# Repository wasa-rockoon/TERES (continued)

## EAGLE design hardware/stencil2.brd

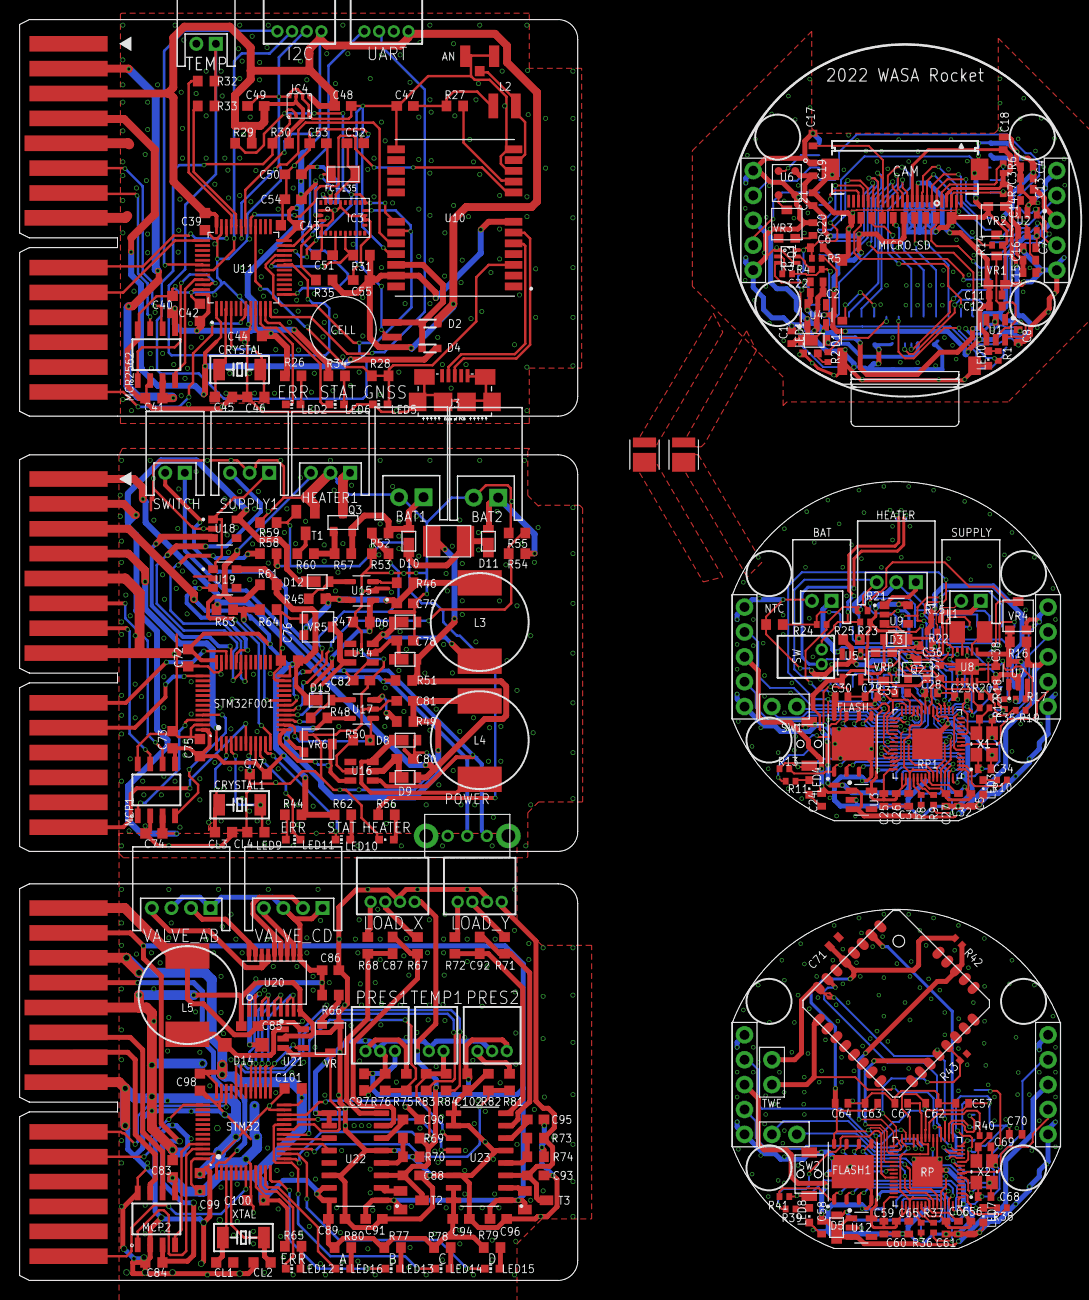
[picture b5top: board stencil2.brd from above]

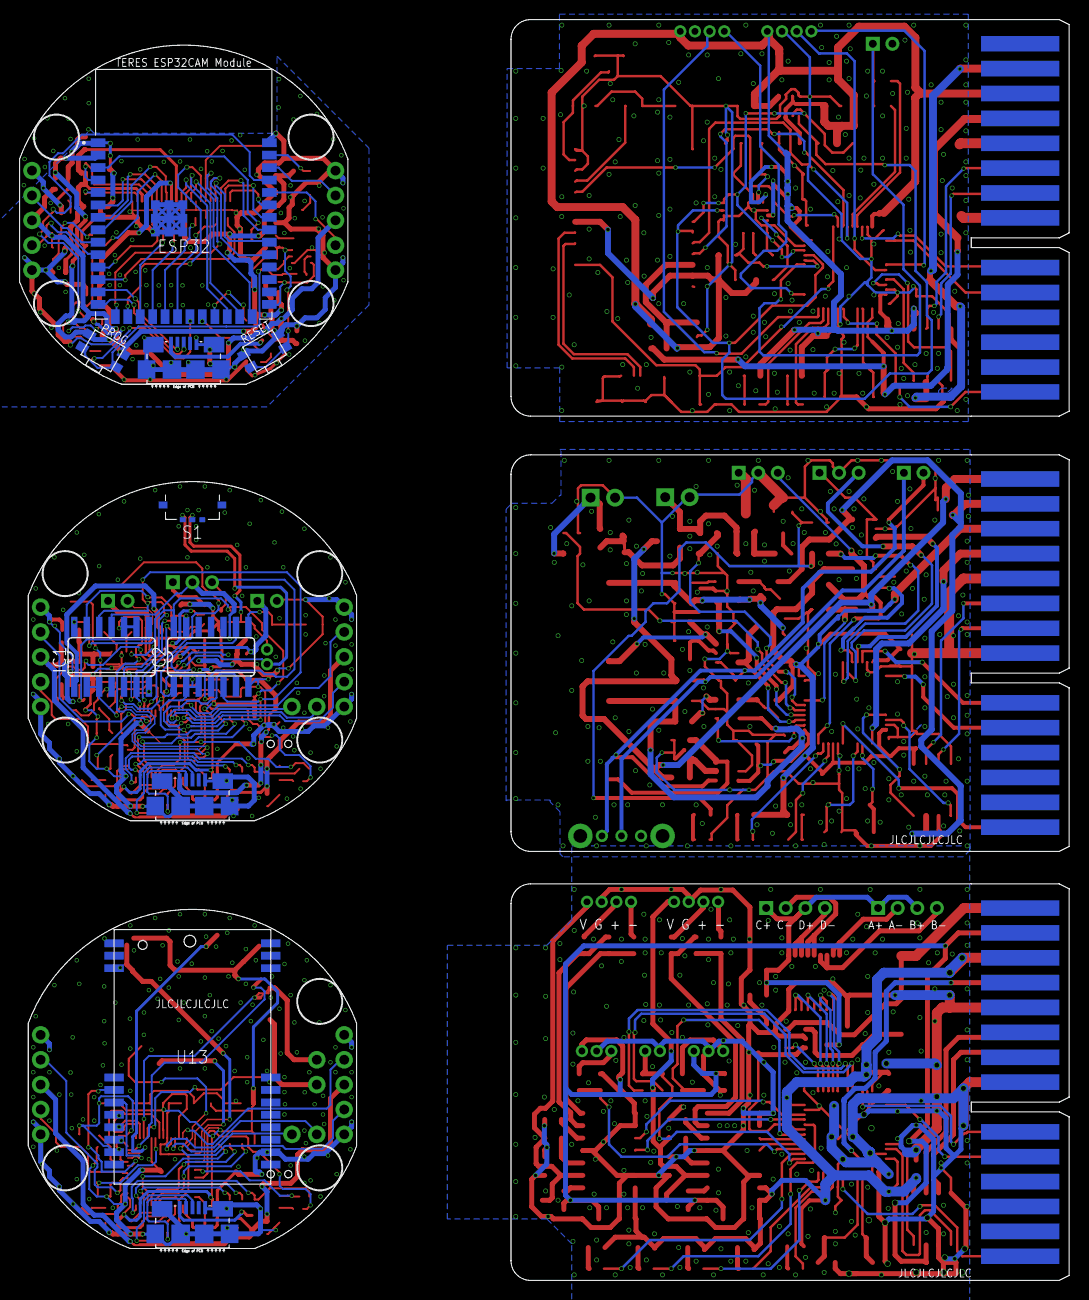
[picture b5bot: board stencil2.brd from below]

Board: 2 copper layers, 107.2 x 128.8 mm, 331 parts (10 on the bottom side), 303 nets.

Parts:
AB: S4B-PH-K-S
AN: U.FL-R-SMT; U.FL_SMT
BAT: S2B-PH-K-S
BAT1, BAT2: S2B-XH-A
BOTTOM, BOTTOM1: P5_2.54
C1, C4, C6, C7, C13, C18, C19, C24, C37, C58: 0.1µF; C0402
C2, C21, C25, C30, C36, C38, C59: 10µF; C0402
C3: 22µF; C0402
C5, C23, C27, C28, C29, C32, C33, C56, C57, C61, C62, C63, C70, C71: 0.1µ; C0402
C8, C14: 0.01µF; C0402
C9, C10: P5_2.54
C11, C20: 2.2µF; C0402
C12, C16: 100pF; C0402
C15: 1.0µF; C0402
C17: 15pF; C0402
C22: 1µF; C0402
C26, C31, C60, C65: 1µ; C0402
C34, C35: 10p; C0402
C39, C40, C41, C42, C43, C44, C72, C73, C74, C75, C76, C77, C83, C84, C98, C99, C100, C101: C0603K
C45, C46: 15pF; C0603K
C47: 47pF; C0603
C48, C49, C50, C51, C55: 0.1µ; C0603
C52, C53, C97, C102: C0603
C54, C82, C87, C89, C90, C92, C94, C95: 0.1µF; C0603
C64, C68, C69: 0.1μ; C0402
C66, C67: 1μ; C0402
C78, C79, C80, C81: 47µF; C0603
C85: 4.7µF; C0603
C86: 2.2µF; C0603
C88, C91, C93, C96: 10µF; C0603
CAM: OV2640_FPC_INV; FH12-24S-0.5SH
CD: S4B-PH-K-S
CELL: DCK-3R3E; DC,DCK
CL1, CL2, CL3, CL4: 15pF; C0603K
CRYSTAL, CRYSTAL1: 32.768kHz; FC-255
D1, D3, D5, D6, D7, D8, D9, D10, D11, D12, D13: CUHS20S30
D2, D4: RB521S-30TE61; SODFL1608X70N
D14: SOD123
ESP32: ESP32-S3-WROOM-1-N16R2; XCVR_ESP32-S3-WROOM-1-N16R2
FC-135: FC-135
FLASH, FLASH1: W25Q32JVZPIQ; SON127P600X500X80-9N
HEATER, HEATER1: S3B-PH-K-S
I2C: S4B-ZR
IC1, IC2: 4066D; SO14
IC3: BN055; LGA-28_3.80X5.20/0.5
IC4: BME280
J1, J2, J3, J4: MICRO_USB_B_HIROSE_ZX62-B-5PA(11)MODEL; GHI-CONNECTORS_10118192-0001LF(MICRO-USB-B-AMPHENOL-FCI)
L1: 4.7µH; L3225M
L2: 33Ω; SM-NE29
L3, L4: 22µH; NR10050
L5: 10µH; NR10050
LED0, LED1, LED3, LED4, LED7, LED8, LED10: CHIPLED_0603
LED2, LED5, LED6, LED9, LED11, LED12, LED13, LED14, LED15, LED16: CHIP-LED0603
LOAD_X: S4B-ZR
LOAD_Y: S4B-ZR
MCP1, MCP2, MCP2562: MCP2562-E/SN; SOIC127P600X175-8N
MICRO_SD: DM3AT-SF-PEJM5; HRS_DM3AT-SF-PEJM5
NTC: 10k; R0603
POWER: SK-12D01-VG4
PRES1, PRES2: S3B-ZR
PROG: THAF01-NC-R
Q1: HN1C01FU; SOT-363
Q2, Q3: IRLML6402; SOT-23
R1, R2, R12, R13, R14, R38, R39, R40, R41: 1k; R0402
R3, R4, R5, R6, R7, R18, R21, R24, R42, R43: 10k; R0402
R8, R9: 27.4; R0402
R10, R17, R23: 100; R0402
R11: 220; R0402
R15, R19, R20, R22: 100k; R0402
R16, R25, R45, R48: 0.033; R0603
R26, R28, R29, R30, R31, R34, R35: R0603
R27: 10; R0603
R32, R47, R50, R51, R57, R59, R61, R70, R74, R75, R81, R83: 10k; R0603
R33, R53, R55, R64, R84: 100k; R0603
R36, R37: 27Ω; R0402
R44, R58, R60, R62, R65, R77, R78, R79, R80: 1k; R0603
R46, R49, R67, R68, R71, R72: 100; R0603
R52, R54, R63, R66: 1M; R0603
R56: 470; R0603
R69, R73: 22k; R0603
R76, R82: 15k; R0603
RESET: THAF01-NC-R
RP, RP1: RP2040; QFN40P700X700X90-57N
S1: SSAJ120100
STM32, STM32F001: STM32F072-LQFP48; LQFP48
SUPPLY: S2B-PH-K-S
SUPPLY1: S3B-PH-K-S
SW: S2B-ZR
SW1, SW2: TVAF06-A020B-R
SWITCH: S2B-PH-K-S
T1: SOT23-EBC
T2, T3: SOT23-BEC
TEMP: S2B-PH-K-S
TEMP1: S2B-ZR
TOP, TOP1: P5_2.54
TWE: P2_2_2.54; P2_2.54
U1, U2: NJM11100; SOT95P240X110-6N
U3, U4, U12: NJM12888F; SOT95P240X110-5N
U5: MCP73831; SOT23-5L
U6: SPU0414HR5H-SB
U7, U15, U17: LT6106CS5#PBF; SOT95P280X100-5N_LT6106CS5#PBF
U8: TPS63000; 10-VFDFN
U9, U18, U19: TCK106AF,LF; IC_TCK106AF,LF
U10: NEO-M9N-00B; XCVR_NEO-M9N-00B
U11: STM32L433CCT6; QFP50P900X900X160-48N
U13: E220-900T22S
U14, U16: LT1616ES6TRMPBF; SOT-6_S
U20: TD62083AFNG; SSOP18-P-225-0.65
U21: LT1930; SOT95P240X110-5N
U22, U23: HX711; SOP127P600X180-16N
U$1, U$7, U$9: EDGE30
U$2, U$5: P2_2_2.54; P2_2.54
U$3, U$4: S1S0-3030XX9506
U$6: LITE
U$8: SMD1812P125TS; SMD1812P
UART: S4B-ZR
VR, VR1, VR2, VR3: 100k; PVZ3A
VR4, VR5, VR6: 22k; PVZ3A
VRP: 10k; PVZ3A
X1, X2: FA-238
XTAL: 32.768kHz; FC-255

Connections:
1.5V: C11.1, C12.1, CAM.10, U1.4, VR1.1
1PPS: LED5.A, R28.1, R28.2, U10.3, U11.28
1V1: C65.1, C66.1, C67.1, RP.23, RP.45, RP.50
1V2: C31.1, C32.1, C33.1, RP1.23, RP1.45, RP1.50
2.8V: C15.1, C16.1, C18.1, CAM.4, CAM.11, R6.1, R7.2, U2.4, VR2.1
3V3: C81.1, L4.2, R48.1, R49.2, U17.5, VR6.3
5V: C79.1, L3.2, R45.1, R46.2, U15.5, VR5.3
!SHDN!: C82.1, POWER.B, SWITCH.2, U14.4, U16.4
ADC0_IN: IC1.2, IC1.3, RP1.38
ADC1_IN: IC1.9, IC1.10, RP1.39
ADC2_IN: IC2.2, IC2.3, IC2.9, RP1.40
ADC_SEL1: IC1.6, IC1.13, IC2.13, RP1.16
ADC_SEL2: IC1.5, IC1.12, IC2.5, RP1.31
ADC_SEL3: IC2.6, RP1.29
ANT: AN.SIG, L2.2, U10.11
A_OUT: AB.2, U20.P17, U20.P18
BAT1: BAT1.1, D10.A, Q3.P2, R52.2, R57.2
BAT1_V: R52.1, R53.2, STM32F001.18
BAT2: BAT2.1, D11.A, R54.2
BAT2_V: R54.1, R55.2, STM32F001.17
BAT_V: IC1.4, R19.1, R20.2
BNO_!RESET!: IC3.11, R31.1, U11.20
B_OUT: AB.4, U20.P15, U20.P16
CAM_POWER: ESP32.37, U1.1, U2.1
CAM_RESET: CAM.6, ESP32.6
CANH1: MCP2562.7, U$1.7
CANH2: MCP1.7, U$7.7
CANH3: MCP2.7, U$9.7
CANL1: MCP2562.6, U$1.6
CANL2: MCP1.6, U$7.6
CANL3: MCP2.6, U$9.6
CAN_RX: MCP2562.4, U11.45
CAN_RX1: MCP1.4, STM32F001.45
CAN_RX2: MCP2.4, STM32.45
CAN_TX: MCP2562.1, U11.46
CAN_TX1: MCP1.1, STM32F001.46
CAN_TX2: MCP2.1, STM32.46
CHARGE: RP1.18, U5.1
C_OUT: CD.2, U20.P13, U20.P14
D0: CAM.19, ESP32.32
D1: CAM.21, ESP32.34
D2: CAM.22, ESP32.35
D3: CAM.20, ESP32.33
D4: CAM.18, ESP32.31
D5: CAM.16, ESP32.16
D6: CAM.14, ESP32.26
D7: CAM.12, ESP32.24
D_OUT: CD.4, U20.P11, U20.P12
EN: C6.1, ESP32.3, Q1.6, R5.1, RESET.3, RESET.4
EN1: C37.1, S1.2, SW.2, U8.6, U8.7, U8.8
GND: C1.2, C2.2, C3.2, C4.2, C6.2, C7.2, C8.2, C9.1, C9.5, C10.1, C10.5, C11.2, C13.2, C14.2, C15.2, C17.2, C18.2, C19.2, C20.2, C21.2, C22.2, CAM.2, CAM.15, CAM.PAD1, CAM.PAD2, ESP32.1, ESP32.40, ESP32.41_1, ESP32.41_2, ESP32.41_3, ESP32.41_4, ESP32.41_5, ESP32.41_6, ESP32.41_7, ESP32.41_8, ESP32.41_9, J1.CGND1, J1.CGND2, J1.CGND3, J1.CGND4, J1.CGND5, J1.CGND6, J1.GND, LED0.C, LED1.C, MICRO_SD.6, MICRO_SD.P1, MICRO_SD.P2, MICRO_SD.P3, MICRO_SD.P4, MICRO_SD.SWB, Q1.1, Q1.4, R14.2, RESET.1, RESET.2, U1.2, U2.2, U4.2, U6.2, VR1.3, VR2.3
GND1: BAT.2, BOTTOM.1, BOTTOM.5, C5.2, C23.2, C24.2, C25.2, C26.2, C27.2, C28.2, C29.2, C30.2, C31.2, C32.2, C33.2, C34.2, C35.2, C36.2, C37.2, C38.2, FLASH.4, FLASH.9, IC1.7, IC2.7, J2.CGND1, J2.CGND2, J2.CGND3, J2.CGND4, J2.CGND5, J2.CGND6, J2.GND, LED3.C, LED4.C, NTC.1, R18.1, R20.1, R22.1, R25.1, RP1.19, RP1.57, SUPPLY.2, SW1.P$1, TOP.1, TOP.5, U3.2, U5.2, U7.2, U8.3, U8.9, U8.P$1, U8.P$2, U8.P$3, U8.P$4, U8.P$5, U9.2, VR4.3, VRP.1, X1.2, X1.4
GND2: AN.GND1, AN.GND2, C39.2, C40.2, C41.2, C42.2, C43.2, C44.2, C45.1, C46.1, C47.2, C48.2, C49.2, C50.2, C51.2, C52.1, C53.1, C54.2, C55.2, CELL.-, I2C.2, IC3.2, IC3.5, IC3.6, IC3.17, IC3.18, IC3.25, IC4.1, IC4.5, IC4.7, J3.CGND1, J3.CGND2, J3.CGND3, J3.CGND4, J3.CGND5, J3.CGND6, J3.GND, LED5.C, MCP2562.2, MCP2562.8, TEMP.2, U10.10, U10.12, U10.13, U10.24, U11.8, U11.23, U11.35, U11.47, U$1.5, U$1.8, UART.2
GND3: BOTTOM1.1, BOTTOM1.5, C56.2, C57.2, C58.2, C59.2, C60.2, C61.2, C62.2, C63.2, C64.2, C65.2, C66.2, C67.2, C68.2, C69.2, C70.2, C71.2, FLASH1.4, FLASH1.9, J4.CGND1, J4.CGND2, J4.CGND3, J4.CGND4, J4.CGND5, J4.CGND6, J4.GND, LED7.C, LED8.C, R43.1, RP.19, RP.57, SW2.P$1, TOP1.1, TOP1.5, U12.2, U13.P1, U13.P2, U13.P3, U13.P4, U13.P11, U13.P13, U13.P19, U13.P20, U13.P22, U$6.20, U$6.28, X2.2, X2.4
GND4: BAT1.2, BAT2.2, C72.2, C73.2, C74.2, C75.2, C76.2, C77.2, C78.2, C79.2, C80.2, C81.2, C82.2, CL3.1, CL4.1, D6.A, D8.A, HEATER1.2, LED10.C, MCP1.2, MCP1.8, R47.1, R50.1, R53.1, R55.1, R59.1, R64.1, STM32F001.8, STM32F001.23, STM32F001.35, STM32F001.47, SUPPLY1.2, T1.E, U14.2, U15.2, U16.2, U17.2, U18.2, U19.2, U$7.5, U$7.8, VR5.1, VR6.1
GND5: C83.2, C84.2, C85.2, C86.2, C88.2, C89.2, C90.2, C91.2, C93.2, C94.2, C95.2, C96.2, C97.2, C98.2, C99.2, C100.2, C101.2, C102.2, CL1.1, CL2.1, LOAD_X.2, LOAD_Y.2, MCP2.2, MCP2.8, PRES1.2, PRES2.2, R70.1, R74.1, R76.1, R82.1, STM32.8, STM32.23, STM32.35, STM32.47, TEMP1.2, U20.P9, U21.2, U22.5, U22.9, U22.10, U22.14, U23.5, U23.9, U23.10, U23.14, U$9.5, U$9.8, VR.1
GPS_!RESET!: U10.8, U11.29
GPS_RTX: U10.20, U11.31
GPS_TRX: U10.21, U11.30
HEATER: RP1.17, U9.3
HEATER1: R58.1, STM32F001.30
HEATER+: HEATER1.1, Q3.P3
HEATER_I: HEATER.2, IC1.11, R25.2
HEATER_OUT: HEATER.1, U9.1
HSYNC: CAM.9, ESP32.8
I2C1_SCL: I2C.4, U11.42
I2C1_SDA: I2C.3, U11.43
I2C2_SCL: IC3.19, IC4.4, R30.1, U10.19, U11.21
I2C2_SDA: IC3.20, IC4.3, R29.1, U10.18, U11.22
I2C_SCL: CAM.5, ESP32.4, R6.2
I2C_SDA: CAM.3, ESP32.5, R7.1
IO0: C22.1, ESP32.27, Q1.3
LED0: ESP32.21, R1.2
LED1: ESP32.22, R2.2
LED2: R10.2, RP1.2
LED3: R11.2, RP1.37
LED4: R38.2, RP.2
LED5: R39.2, RP.37
LORA_AUX: RP.14, U13.P9
LORA_M0: RP.9, U13.P5
LORA_M1: RP.11, U13.P6
LORA_RTX: RP.16, U13.P8
LORA_TRX: RP.15, U13.P7
MIC: ESP32.39, U6.4
unnamed: C8.1, U1.3
unnamed: C12.2, U1.5, VR1.2
unnamed: C14.1, U2.3
unnamed: C16.2, U2.5, VR2.2
unnamed: PROG.3, PROG.4, R3.1, R4.1
unnamed: LED3.A, R10.1
unnamed: LED0.A, R1.1
unnamed: LED1.A, R2.1
unnamed: Q1.2, R3.2
unnamed: CAM.8, R14.1
unnamed: Q1.5, R4.2
unnamed: LED4.A, R11.1
unnamed: U6.3, VR3.2
unnamed: C20.1, VR3.3
unnamed: C35.1, R12.1, X1.1
unnamed: U5.5, VRP.2
unnamed: R17.1, U7.3
unnamed: L1.1, U8.4
unnamed: L1.2, U8.2
unnamed: R23.2, S1.C, SW.1
unnamed: U11.7, U$1.15
unnamed: R27.2, U10.9
unnamed: C47.1, L2.1, R27.1
unnamed: CELL.+, D2.1, D4.1, U10.22
unnamed: C51.1, IC3.9
unnamed: C53.2, FC-135.P$2, IC3.27
unnamed: C52.2, FC-135.P$1, IC3.26
unnamed: LED6.C, U11.11
unnamed: LED6.A, R34.2
unnamed: IC3.4, R35.1
unnamed: LED2.C, U11.10
unnamed: D5.A, J4.VBUS
unnamed: LED7.A, R38.1
unnamed: LED8.A, R39.1
unnamed: C69.1, R40.1, X2.1
unnamed: CL4.2, CRYSTAL1.1, STM32F001.4
unnamed: R46.1, U15.3
unnamed: R49.1, U17.3
unnamed: POWER.C, R51.1, SWITCH.1
unnamed: SUPPLY1.1, U18.1, U19.1
unnamed: LED10.A, R56.2
unnamed: Q3.P1, R57.1, R60.1
unnamed: R56.1, R58.2, R59.2, T1.B
unnamed: R60.2, T1.C
unnamed: LED11.C, STM32F001.11
unnamed: LED11.A, R62.2
unnamed: LED12.C, STM32.10
unnamed: LED12.A, R65.2
unnamed: D14.A, L5.2, U21.1
unnamed: R66.1, VR.3
unnamed: C87.2, R67.1, U22.7
unnamed: C87.1, R68.1, U22.8
unnamed: T2.B, U22.2
unnamed: C90.1, U22.6
unnamed: R69.1, R70.2, U22.4
unnamed: C92.2, R71.1, U23.7
unnamed: C92.1, R72.1, U23.8
unnamed: T3.B, U23.2
unnamed: C95.1, U23.6
unnamed: R73.1, R74.2, U23.4
unnamed: PRES1.3, R75.2
unnamed: LED13.C, STM32.12
unnamed: LED13.A, R77.2
unnamed: LED14.C, STM32.20
unnamed: LED14.A, R78.2
unnamed: C46.2, CRYSTAL.1, U11.4
unnamed: C45.2, CRYSTAL.2, U11.3
unnamed: CL3.2, CRYSTAL1.2, STM32F001.3
unnamed: LED9.C, STM32F001.10
unnamed: LED2.A, R26.2
unnamed: LED15.C, STM32.14
unnamed: LED9.A, R44.2
unnamed: LED15.A, R79.2
unnamed: CL2.2, STM32.4, XTAL.1
unnamed: CL1.2, STM32.3, XTAL.2
unnamed: LED16.C, STM32.11
unnamed: LED16.A, R80.2
unnamed: PRES2.3, R81.2
NRST: STM32.7, U$9.15
NRST1: STM32F001.7, U$7.15
OB_TEMP: IC2.8, NTC.2, R24.1
PCLK: C17.1, CAM.17, ESP32.15
POWER_FB: STM32.19, U21.3, VR.2
POWER_ON: STM32.25, U21.4
PRESSURE_1: R75.1, R76.2, STM32.18
PRESSURE_2: R81.1, R82.2, STM32.15
QSPI_SCLK: FLASH.6, RP1.52
QSPI_SCLK1: FLASH1.6, RP.52
QSPI_SD0: FLASH.5, RP1.53
QSPI_SD1: FLASH.2, RP1.55
QSPI_SD2: FLASH.3, RP1.54
QSPI_SD3: FLASH.7, RP1.51
QSPI_SD4: FLASH1.5, RP.53
QSPI_SD5: FLASH1.2, RP.55
QSPI_SD6: FLASH1.3, RP.54
QSPI_SD7: FLASH1.7, RP.51
QSPI_SS: FLASH.1, R13.2, RP1.56
QSPI_SS1: FLASH1.1, R41.2, RP.56
RX0: C9.4, ESP32.36
RX1: C10.4, ESP32.10
RX2: RP1.28, TOP.4
RX3: BOTTOM.4, RP1.7
RX4: RP.28, TOP1.4
RX5: BOTTOM1.4, RP.7
SD: ESP32.23, MICRO_SD.SWA
SDIO_D1: ESP32.12, MICRO_SD.8
SDIO_D2: ESP32.11, MICRO_SD.1
SPI0_CS: ESP32.17, MICRO_SD.2
SPI0_MISO: ESP32.20, MICRO_SD.7
SPI0_MOSI: ESP32.18, MICRO_SD.3
SPI0_SCK: ESP32.19, MICRO_SD.5
SUPPLY_3V3: STM32F001.32, U19.3
SUPPLY_5V: STM32F001.33, U18.3
SUPPLY_CON: STM32F001.31, SUPPLY1.3
SUPPLY_V: IC1.1, R15.1, R22.2
SW: R13.1, RP1.35, SW1.P$2
SW1: R41.1, RP.35, SW2.P$2
SWCLK: RP1.24, U$2.P$1
SWCLK1: U11.37, U$1.11
SWCLK2: RP.24, U$5.P$1
SWCLK3: STM32F001.37, U$7.11
SWCLK4: STM32.37, U$9.11
SWD: RP1.25, U$2.P$2
SWD1: RP.25, U$5.P$2
SWDIO1: U11.34, U$1.10
SWDIO2: STM32F001.34, U$7.10
SWDIO3: STM32.34, U$9.10
TEMP: HEATER.3, IC2.4, R21.1
TEMP1: R32.1, R33.1, TEMP.1, U11.19
TEMP2: HEATER1.3, R61.1, STM32F001.12
TEMP3: R83.1, R84.1, STM32.13, TEMP1.1
TEMP_HIGH: R32.2, U11.33
TEMP_HIGH1: R83.2, STM32.32
TEMP_LOW: R33.2, U11.32
TEMP_LOW1: R84.2, STM32.31
TWE_BPS: RP.31, U$6.19
TWE_PGM: RP.12, U$6.2
TWE_RESET: R43.2, RP.30, U$6.21
TWE_RTS: RP.13, U$6.7
TWE_RTX: RP.17, TWE.P$2, U$6.8
TWE_SLEEP: R42.1, RP.29, U$6.27
TWE_TRX: RP.18, TWE.P$1, U$6.9
TX0: C9.2, ESP32.38
TX1: C10.2, ESP32.9
TX2: RP1.27, TOP.2
TX3: BOTTOM.2, RP1.6
TX4: RP.27, TOP1.2
TX5: BOTTOM1.2, RP.6
UART_RTX: U11.13, UART.4
UART_TRX: U11.12, UART.3
USB_D+: J3.D+, U10.6
USB_D-: J3.D-, U10.5
USB_DM: ESP32.13, J1.D-
USB_DM1: J2.D-, R8.2
USB_DM2: J4.D-, R36.2
USB_DM_1: R8.1, RP1.46
USB_DM_2: R36.1, RP.46
USB_DP: ESP32.14, J1.D+
USB_DP1: J2.D+, R9.2
USB_DP2: J4.D+, R37.2
USB_DP_1: R9.1, RP1.47
USB_DP_2: R37.1, RP.47
USB_VCC: D1.A, J1.VBUS
V+: C1.1, C7.1, C9.3, C10.3, C13.1, D1.C, U1.6, U2.6, U4.1, U4.3
V+1: BOTTOM.3, C24.1, R16.2, TOP.3, U3.1, U3.3, U7.4
V+2: BOTTOM1.3, C58.1, D5.C, TOP1.3, U12.1, U12.3
V+3: STM32.1, U$9.4
V+_I: IC1.8, R18.2, U7.1
V+_V: IC2.1, U8.10, VR4.2
VALVE_A: STM32.29, U20.P1, U20.P2
VALVE_B: STM32.28, U20.P3, U20.P4
VALVE_C: STM32.27, U20.P5, U20.P6
VALVE_D: STM32.26, U20.P7, U20.P8
VBAT: BAT.1, Q2.P3, R19.2, U5.3
VBAT1: D4.2, U11.1, U$1.4
VBAT2: STM32F001.1, U$7.4
VBAT_: C36.1, D3.C, Q2.P2, R23.1, U8.5, U9.5
VCC: C41.1, MCP2562.3, U$1.2
VCC1: C74.1, D12.C, MCP1.3, U18.5, U$7.2
VCC2: C84.1, C91.1, C96.1, C97.1, C102.1, MCP2.3, PRES1.1, PRES2.1, T2.E, T3.E, U22.1, U23.1, U$9.2
VCC': D12.A, R45.2, U15.4
VCC_I: R47.2, STM32F001.16, U15.1
VCC_IN: C78.1, D7.C, U14.5
VCC_SW: D6.C, L3.1, U14.6
VCC_V: STM32F001.15, U14.3, VR5.2
VDD: C2.1, C3.1, C4.1, C19.1, C21.1, ESP32.2, MICRO_SD.4, PROG.1, PROG.2, R5.2, U4.5, U6.1
VDD1: C5.1, C23.1, C25.1, C26.1, C27.1, C28.1, C29.1, C30.1, FLASH.8, IC1.14, IC2.14, R21.2, R24.2, RP1.1, RP1.10, RP1.22, RP1.26, RP1.33, RP1.42, RP1.43, RP1.44, RP1.48, RP1.49, U3.5
VDD2: C39.1, C40.1, C42.1, C43.1, C44.1, C48.1, C49.1, C50.1, C54.1, C55.1, D2.2, I2C.1, IC3.3, IC3.28, IC4.2, IC4.6, IC4.8, MCP2562.5, R26.1, R29.2, R30.2, R31.2, R34.1, R35.2, U10.7, U10.23, U11.9, U11.24, U11.36, U11.48, U$1.3, UART.1
VDD3: C56.1, C57.1, C59.1, C60.1, C61.1, C62.1, C63.1, C64.1, C70.1, C71.1, FLASH1.8, R42.2, RP.1, RP.10, RP.22, RP.26, RP.33, RP.42, RP.43, RP.44, RP.48, RP.49, U12.5, U13.P10, U$6.5
VDD4: C72.1, C73.1, C75.1, C76.1, C77.1, D13.C, MCP1.5, R44.1, R61.2, R62.1, STM32F001.9, STM32F001.24, STM32F001.36, STM32F001.48, U19.5, U$7.3
VDD5: C83.1, C89.1, C94.1, C98.1, C99.1, C100.1, C101.1, MCP2.5, R65.1, R77.1, R78.1, R79.1, R80.1, STM32.9, STM32.24, STM32.36, STM32.48, U22.15, U22.16, U23.15, U23.16, U$9.3
VDD': D13.A, R48.2, U17.4
VDD_I: R50.2, STM32F001.14, U17.1
VDD_IN: C80.1, D9.C, U16.5
VDD_SW: D8.C, L4.1, U16.6
VDD_V: STM32F001.13, U16.3, VR6.2
VOUT: C38.1, R16.1, R17.2, U7.5, U8.1, VR4.1
VPP: D3.A, J2.VBUS, Q2.P1, R15.2, SUPPLY.1, U5.4
VPP2: D7.A, D9.A, R51.2, R63.2, U$7.1, U$8.2
VPP3: C85.1, L5.1, U21.5, U$9.1
VPP_IN: D10.C, D11.C, U$8.1
VPP_V: R63.1, R64.2, STM32F001.19
VSYNC: CAM.7, ESP32.7
V_VALVE: AB.1, AB.3, C86.1, CD.1, CD.3, D14.C, R66.2, U20.P10
XCLK: CAM.13, ESP32.25
XIN1: C34.1, RP1.20, X1.3
XIN2: C68.1, RP.20, X2.3
XOUT1: R12.2, RP1.21
XOUT2: R40.2, RP.21
X_DATA: STM32.16, U22.12
X_SCK: STM32.17, U22.11
X_SIG+: LOAD_X.4, R68.2
X_SIG-: LOAD_X.3, R67.2
X_VDD: C88.1, LOAD_X.1, R69.2, T2.C, U22.3
Y_DATA: STM32.21, U23.12
Y_SCK: STM32.22, U23.11
Y_SIG+: LOAD_Y.4, R72.2
Y_SIG-: LOAD_Y.3, R71.2
Y_VDD: C93.1, LOAD_Y.1, R73.2, T3.C, U23.3

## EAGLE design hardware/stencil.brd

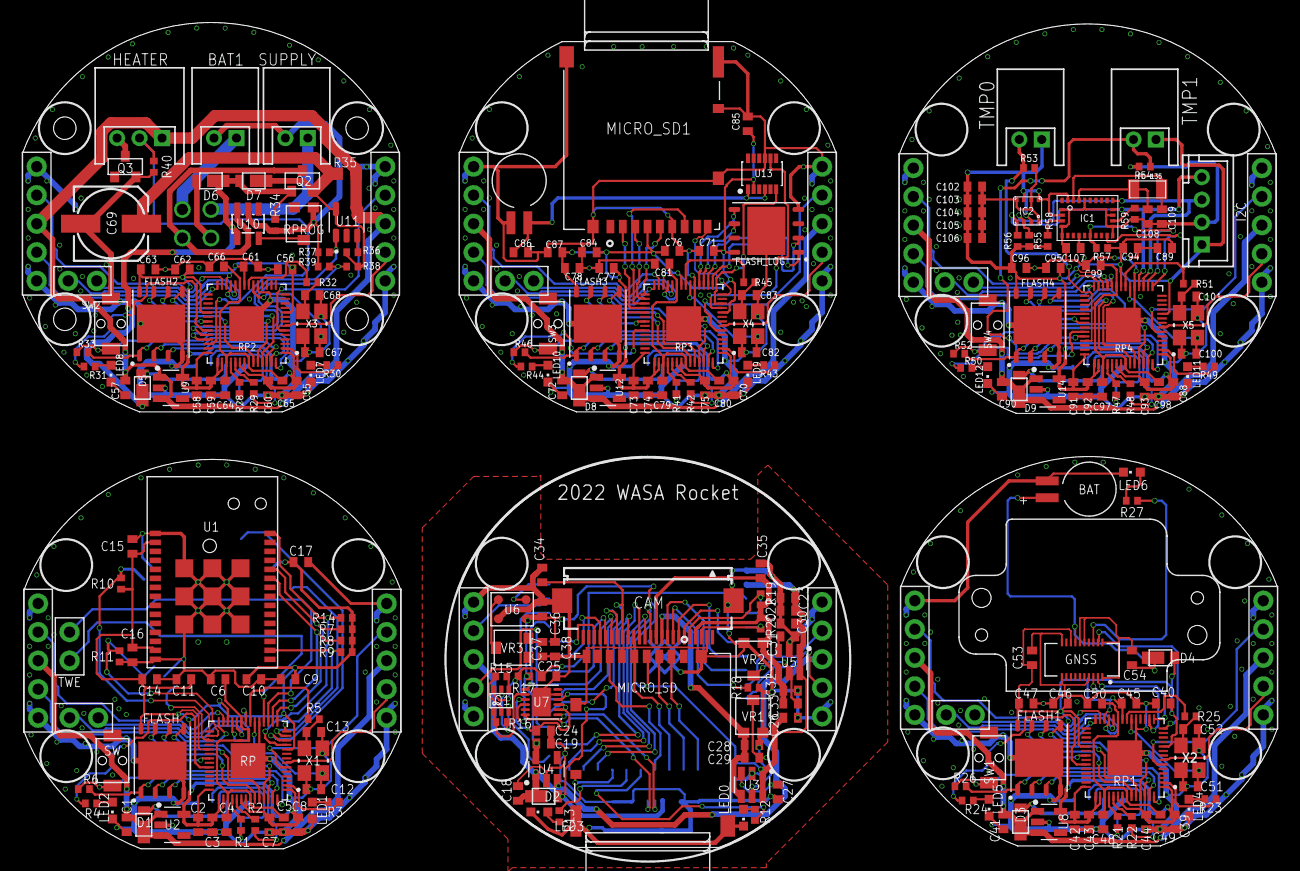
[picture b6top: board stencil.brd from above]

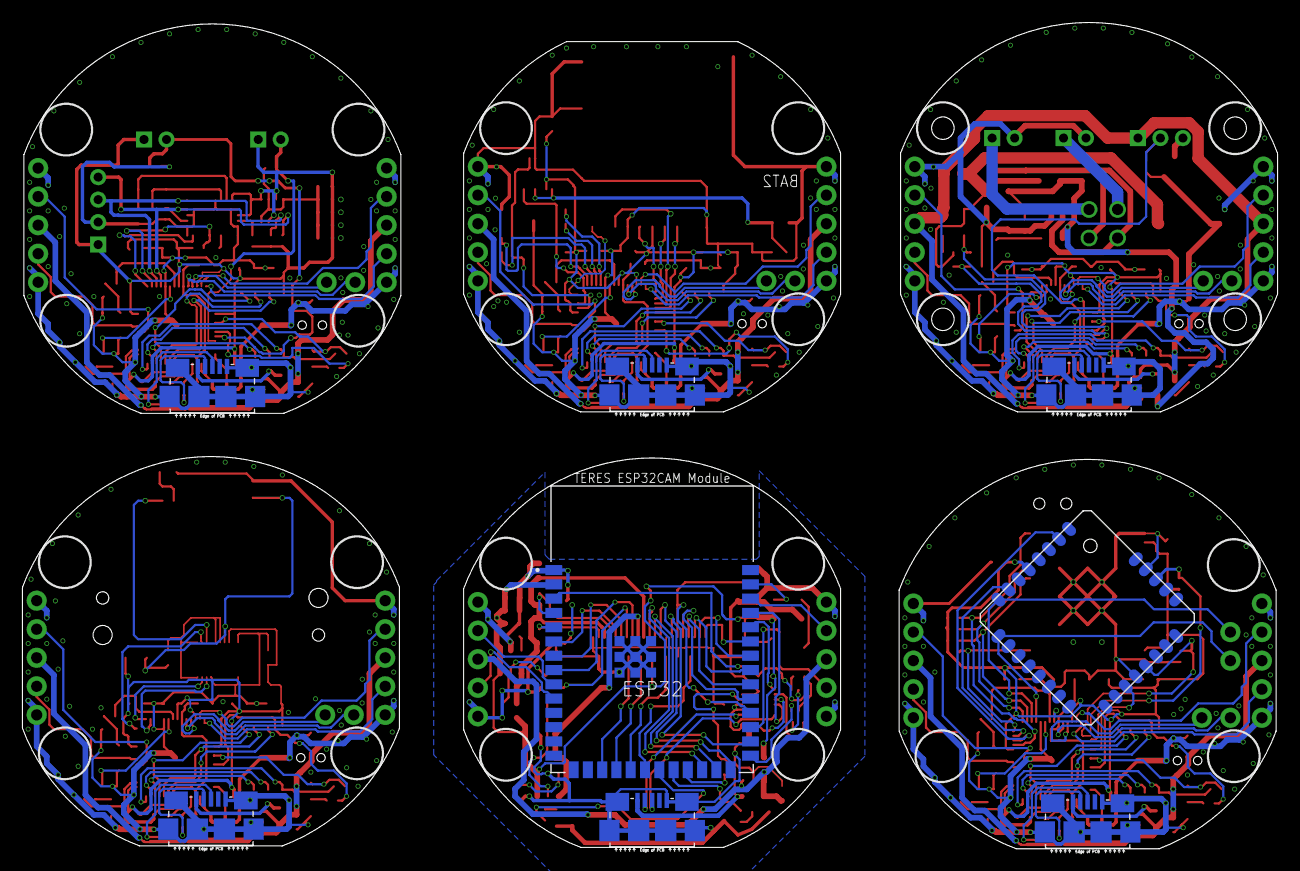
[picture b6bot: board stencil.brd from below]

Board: 2 copper layers, 111.6 x 73.5 mm, 271 parts (8 on the bottom side), 247 nets.

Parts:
BAT, BAT2: MS414GE-FL26E; BAT_MS414GE-FL26E
BAT1: S2B-PH-K-S
BOTTOM, BOTTOM1, BOTTOM2, BOTTOM3, BOTTOM4: P5_2.54
C1, C18, C23, C24, C25, C26, C30, C35, C36, C41, C57, C72, C86, C87, C90: 0.1µF; C0402
C2, C19, C38, C42, C58, C63, C73, C84, C91: 10µF; C0402
C3, C4, C43, C48, C59, C64, C74, C79, C92, C97: 1µ; C0402
C5, C6: 1μ; C0402
C7, C8, C9, C10, C11, C15, C16, C17, C39, C40, C44, C45, C46, C53, C54, C55, C56, C60, C61, C62, C65, C66, C70, C71, C75, C76, C77, C88, C89, C93, C94, C95, C102, C103, C104, C107: 0.1µ; C0402
C12, C13, C14: 0.1μ; C0402
C20, C21: P5_2.54
C22: 22µF; C0402
C27, C31: 0.01µF; C0402
C28, C37: 2.2µF; C0402
C29, C33: 100pF; C0402
C32: 1.0µF; C0402
C34: 15pF; C0402
C47, C49, C50, C51, C52, C78, C80, C81, C82, C83, C85, C96, C98, C99, C100, C101, C108, C109: C0402
C67, C68: 10p; C0402
C69: 153CLV-0605
C105: 6.8n; C0402
C106: 0.12u; C0402
CAM: OV2640_FPC_INV; FH12-24S-0.5SH
D1, D2, D3, D4, D5, D6, D7, D8, D9: CUHS20S30
ESP32: ESP32-S3-WROOM-1-N16R2; XCVR_ESP32-S3-WROOM-1-N16R2
FC-135: FC-135
FLASH, FLASH1, FLASH2, FLASH3, FLASH4: W25Q32JVZPIQ; SON127P600X500X80-9N
FLASH_LOG: W25Q32JVZPIQ; SON127P600X500X80-9N
GNSS: GYSFDMAXB
HEATER: S3B-PH-K-S
I2C: B4B-PH-K-S
IC1: BN055; LGA-28_3.80X5.20/0.5
IC2: BME280
J1, J2, J3, J4, J5, J6: MICRO_USB_B_HIROSE_ZX62-B-5PA(11)MODEL; GHI-CONNECTORS_10118192-0001LF(MICRO-USB-B-AMPHENOL-FCI)
LED0, LED1, LED2, LED3, LED4, LED5, LED6, LED7, LED8, LED9, LED10, LED11, LED12: CHIPLED_0603
MICRO_SD, MICRO_SD1: DM3AT-SF-PEJM5; HRS_DM3AT-SF-PEJM5
Q1: HN1C01FU; SOT-363
Q2: IRLML6402; SOT-23
Q3: IRLML6344; SOT-23
R1, R2: 27Ω; R0402
R3, R4, R5, R6, R18, R25, R26, R32, R33, R45, R46, R51, R52: 1k; R0402
R7, R8, R9, R10, R11, R14, R15, R16, R17, R19, R20, R37: 10k; R0402
R12, R13, R21, R22, R23, R24, R41, R42, R43, R44, R47, R48, R49, R50, R55, R56, R57, R58, R59: R0402
R27, R30, R36: 100; R0402
R28, R29: 27.4; R0402
R31: 220; R0402
R34, R38, R39: 100k; R0402
R35: 0.033; R0603
R40, R53, R54: 22k; R0402
RP, RP1, RP2, RP3, RP4: RP2040; QFN40P700X700X90-57N
RPROG: 10k; PVZ3A
SUPPLY: S2B-PH-K-S
SW, SW1, SW2, SW3, SW4: TVAF06-A020B-R
TMP0, TMP1: S2B-PH-K-S
TOP, TOP1, TOP2, TOP3, TOP4: P5_2.54
TWE: P2_2_2.54; P2_2.54
U1: ES920LR3
U2, U4, U8, U9, U12, U14: NJM12888F; SOT95P240X110-5N
U3, U5: NJM11100; SOT95P240X110-6N
U6: SPU0414HR5H-SB
U7: FT234XD-R; SON45P300X300X80-13N
U10: MCP73831; SOT23-5L
U11: LT6106CS5#PBF; SOT95P280X100-5N_LT6106CS5#PBF
U13: RX-8035LC; VSOJ12
U$1: LITE
U$2, U$3, U$4, U$5, U$6: P2_2_2.54; P2_2.54
VR1, VR2: PVZ3A
VR3: 100k; PVZ3A
X1, X2, X3, X4, X5: FA-238

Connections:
1.3V: C28.1, C29.1, CAM.10, U3.4, VR1.1
1V1: C48.1, C49.1, C50.1, RP1.23, RP1.45, RP1.50
1V2: C4.1, C5.1, C6.1, RP.23, RP.45, RP.50
1V3: C64.1, C65.1, C66.1, RP2.23, RP2.45, RP2.50
1V4: C79.1, C80.1, C81.1, RP3.23, RP3.45, RP3.50
1V5: C97.1, C98.1, C99.1, RP4.23, RP4.45, RP4.50
2.8V: C32.1, C33.1, C35.1, CAM.4, CAM.11, R19.1, R20.2, U5.4, VR2.1
BOOT_LOAD: IC1.4, R58.1
CAM_RESET: CAM.6, ESP32.6
D0: CAM.19, ESP32.32
D1: CAM.21, ESP32.34
D2: CAM.22, ESP32.35
D3: CAM.20, ESP32.33
D4: CAM.18, ESP32.31
D5: CAM.16, ESP32.28
D6: CAM.14, ESP32.26
D7: CAM.12, ESP32.24
DTR: Q1.4, R15.1
EN: C25.1, ESP32.3, Q1.6, R17.1
GND: BOTTOM.1, BOTTOM.5, C1.2, C2.2, C3.2, C4.2, C5.2, C6.2, C7.2, C8.2, C9.2, C10.2, C11.2, C12.2, C13.2, C14.2, C15.2, C16.1, C17.2, FLASH.4, FLASH.9, J1.CGND1, J1.CGND2, J1.CGND3, J1.CGND4, J1.CGND5, J1.CGND6, J1.GND, LED1.C, LED2.C, R11.1, RP.19, RP.57, SW.P$1, TOP.1, TOP.5, U1.P1, U1.P15, U1.P31, U1.P32, U1.P33, U1.P34, U1.P35, U1.P36, U1.P37, U1.P38, U1.P39, U2.2, U$1.20, U$1.28, X1.2, X1.4
GND1: C18.2, C19.2, C20.1, C20.5, C21.1, C21.5, C22.2, C23.2, C24.2, C25.2, C26.2, C27.2, C28.2, C30.2, C31.2, C32.2, C34.2, C35.2, C36.2, C37.2, C38.2, CAM.2, CAM.15, CAM.PAD1, CAM.PAD2, ESP32.1, ESP32.40, ESP32.41_1, ESP32.41_2, ESP32.41_3, ESP32.41_4, ESP32.41_5, ESP32.41_6, ESP32.41_7, ESP32.41_8, ESP32.41_9, J2.CGND1, J2.CGND2, J2.CGND3, J2.CGND4, J2.CGND5, J2.CGND6, J2.GND, LED0.C, LED3.C, MICRO_SD.6, MICRO_SD.P1, MICRO_SD.P2, MICRO_SD.P3, MICRO_SD.P4, MICRO_SD.SWB, R18.2, U3.2, U4.2, U5.2, U6.2, U7.5, U7.13, VR1.3, VR2.3
GND2: BAT.-, BOTTOM1.1, BOTTOM1.5, C39.2, C40.2, C41.2, C42.2, C43.2, C44.2, C45.2, C46.2, C47.2, C48.2, C49.2, C50.2, C51.2, C52.2, C53.2, C54.2, FLASH1.4, FLASH1.9, GNSS.1, GNSS.2, GNSS.7, GNSS.10, GNSS.12, GNSS.19, GNSS.20, J3.CGND1, J3.CGND2, J3.CGND3, J3.CGND4, J3.CGND5, J3.CGND6, J3.GND, LED4.C, LED5.C, LED6.C, RP1.19, RP1.57, SW1.P$1, TOP1.1, TOP1.5, U8.2, X2.2, X2.4
GND3: BAT1.2, BOTTOM2.1, BOTTOM2.5, C55.2, C56.2, C57.2, C58.2, C59.2, C60.2, C61.2, C62.2, C63.2, C64.2, C65.2, C66.2, C67.2, C68.2, C69.-, FLASH2.4, FLASH2.9, J4.CGND1, J4.CGND2, J4.CGND3, J4.CGND4, J4.CGND5, J4.CGND6, J4.GND, LED7.C, LED8.C, Q3.P2, R34.1, R37.1, R39.1, R40.1, RP2.19, RP2.57, RPROG.1, SUPPLY.2, SW2.P$1, TOP2.1, TOP2.5, U9.2, U10.2, U11.2, X3.2, X3.4
GND4: BAT2.-, BOTTOM3.1, BOTTOM3.5, C70.2, C71.2, C72.2, C73.2, C74.2, C75.2, C76.2, C77.2, C78.2, C79.2, C80.2, C81.2, C82.2, C83.2, C84.2, C85.2, C86.2, C87.2, FLASH3.4, FLASH3.9, FLASH_LOG.4, FLASH_LOG.9, J5.CGND1, J5.CGND2, J5.CGND3, J5.CGND4, J5.CGND5, J5.CGND6, J5.GND, LED9.C, LED10.C, MICRO_SD1.6, MICRO_SD1.P1, MICRO_SD1.P2, MICRO_SD1.P3, MICRO_SD1.P4, MICRO_SD1.SWA, RP3.19, RP3.57, SW3.P$1, TOP3.1, TOP3.5, U12.2, U13.9, X4.2, X4.4
GND5: BOTTOM4.1, BOTTOM4.5, C88.2, C89.2, C90.2, C91.2, C92.2, C93.2, C94.2, C95.2, C96.2, C97.2, C98.2, C99.2, C100.2, C101.2, C102.2, C103.2, C104.2, C105.2, C106.2, C107.2, C108.1, C109.1, FLASH4.4, FLASH4.9, I2C.2, IC1.2, IC1.5, IC1.6, IC1.15, IC1.16, IC1.18, IC1.25, IC2.1, IC2.5, IC2.7, J6.CGND1, J6.CGND2, J6.CGND3, J6.CGND4, J6.CGND5, J6.CGND6, J6.GND, LED11.C, LED12.C, R53.1, R54.1, R59.1, RP4.19, RP4.57, SW4.P$1, TOP4.1, TOP4.5, U14.2, X5.2, X5.4
GPS_RESET: GNSS.4, RP1.14
GPS_RTX: GNSS.5, RP1.16
GPS_TRX: GNSS.3, RP1.15
HSYNC: CAM.9, ESP32.8
I2C0_SCL: RP3.12, U13.6
I2C0_SCL1: I2C.4, IC1.19, IC2.4, R56.1, RP4.18
I2C0_SDA2: RP3.11, U13.8
I2C0_SDA3: I2C.3, IC1.20, IC2.3, R55.1, RP4.17
I2C_SCL: CAM.5, ESP32.4, R19.2
I2C_SDA: CAM.3, ESP32.5, R20.1
INT: IC1.14, RP4.15
IO0: ESP32.27, Q1.3
ISENSE: R37.2, RP2.38, U11.1
LED0: R3.2, RP.2
LED1: R4.2, RP.37
LED2: ESP32.21, R12.2
LED3: ESP32.22, R13.2
LED4: R23.2, RP1.2
LED5: R24.2, RP1.37
LED6: R30.2, RP2.2
LED7: R31.2, RP2.37
LED8: R43.2, RP3.2
LED9: R44.2, RP3.37
LED10: R49.2, RP4.2
LED11: R50.2, RP4.37
MIC: ESP32.39, U6.4
unnamed: LED3.A, R13.1
unnamed: Q1.2, R15.2
unnamed: Q1.5, R16.2
unnamed: C27.1, U3.3
unnamed: D1.A, J1.VBUS
unnamed: LED0.A, R12.1
unnamed: LED1.A, R3.1
unnamed: LED2.A, R4.1
unnamed: C29.2, U3.5, VR1.2
unnamed: C13.1, R5.1, X1.1
unnamed: C31.1, U5.3
unnamed: C33.2, U5.5, VR2.2
unnamed: CAM.8, R18.1
unnamed: U6.3, VR3.2
unnamed: C37.1, VR3.3
unnamed: C24.1, U7.2, U7.3, U7.9
unnamed: D3.A, J3.VBUS
unnamed: LED4.A, R23.1
unnamed: LED5.A, R24.1
unnamed: C52.1, R25.1, X2.1
unnamed: BAT.+, C54.1, D4.C, GNSS.14
unnamed: LED6.A, R27.1
unnamed: GNSS.6, R27.2
unnamed: D5.A, J4.VBUS
unnamed: LED7.A, R30.1
unnamed: LED8.A, R31.1
unnamed: C68.1, R32.1, X3.1
unnamed: RPROG.2, U10.5
unnamed: R36.1, U11.3
unnamed: HEATER.3, Q3.P3
unnamed: D8.A, J5.VBUS
unnamed: LED9.A, R43.1
unnamed: LED10.A, R44.1
unnamed: C83.1, R45.1, X4.1
unnamed: BAT2.+, C86.1, U13.1, U13.4
unnamed: D9.A, J6.VBUS
unnamed: LED11.A, R49.1
unnamed: LED12.A, R50.1
unnamed: C101.1, R51.1, X5.1
unnamed: C107.1, IC1.9
unnamed: IC1.17, R59.2
unnamed: C109.2, FC-135.P$2, IC1.27
unnamed: C108.2, FC-135.P$1, IC1.26
PCLK: C34.1, CAM.17, ESP32.30
QSPI_SCLK: FLASH.6, RP.52
QSPI_SCLK1: FLASH1.6, RP1.52
QSPI_SCLK2: FLASH2.6, RP2.52
QSPI_SCLK3: FLASH3.6, RP3.52
QSPI_SCLK4: FLASH4.6, RP4.52
QSPI_SD0: FLASH.5, RP.53
QSPI_SD1: FLASH.2, RP.55
QSPI_SD2: FLASH.3, RP.54
QSPI_SD3: FLASH.7, RP.51
QSPI_SD4: FLASH1.5, RP1.53
QSPI_SD5: FLASH1.2, RP1.55
QSPI_SD6: FLASH1.3, RP1.54
QSPI_SD7: FLASH1.7, RP1.51
QSPI_SD8: FLASH2.5, RP2.53
QSPI_SD9: FLASH2.2, RP2.55
QSPI_SD10: FLASH2.3, RP2.54
QSPI_SD11: FLASH2.7, RP2.51
QSPI_SD12: FLASH3.5, RP3.53
QSPI_SD13: FLASH3.2, RP3.55
QSPI_SD14: FLASH3.3, RP3.54
QSPI_SD15: FLASH3.7, RP3.51
QSPI_SD16: FLASH4.5, RP4.53
QSPI_SD17: FLASH4.2, RP4.55
QSPI_SD18: FLASH4.3, RP4.54
QSPI_SD19: FLASH4.7, RP4.51
QSPI_SS: FLASH.1, R6.2, RP.56
QSPI_SS1: FLASH1.1, R26.2, RP1.56
QSPI_SS2: FLASH2.1, R33.2, RP2.56
QSPI_SS3: FLASH3.1, R46.2, RP3.56
QSPI_SS4: FLASH4.1, R52.2, RP4.56
RESET: IC1.11, R57.1, RP4.16
ROLA_!RESET!: R14.1, RP.11, U1.P30
ROLA_RTX: R8.1, RP.16, U1.P25
ROLA_TRX: R7.1, RP.15, U1.P26
RTS: Q1.1, R16.1, U7.8
RTX: ESP32.36, U7.7
RX0: RP.28, TOP.4
RX1: BOTTOM.4, RP.7
RX2: C20.4, ESP32.29
RX3: C21.4, ESP32.10
RX4: RP1.28, TOP1.4
RX5: BOTTOM1.4, RP1.7
RX6: RP2.28, TOP2.4
RX7: BOTTOM2.4, RP2.7
RX8: RP3.28, TOP3.4
RX9: BOTTOM3.4, RP3.7
RX10: RP4.28, TOP4.4
RX11: BOTTOM4.4, RP4.7
SD: ESP32.23, MICRO_SD.SWA
SD1: MICRO_SD1.SWB, RP3.14
SPI0_CS: ESP32.17, MICRO_SD.2
SPI0_CS3: MICRO_SD1.2, RP3.32
SPI0_MISO: ESP32.20, MICRO_SD.7
SPI0_MISO3: MICRO_SD1.7, RP3.31
SPI0_MOSI: ESP32.18, MICRO_SD.3
SPI0_MOSI3: MICRO_SD1.3, RP3.30
SPI0_SCK: ESP32.19, MICRO_SD.5
SPI0_SCK3: MICRO_SD1.5, RP3.29
SPI1_CS1: FLASH_LOG.1, RP3.16
SPI1_MISO1: FLASH_LOG.2, RP3.15
SPI1_MOSI2: FLASH_LOG.5, RP3.18
SPI1_SCK2: FLASH_LOG.6, RP3.17
SW: R6.1, RP.35, SW.P$2
SW1: R26.1, RP1.35, SW1.P$2
SW2: R33.1, RP2.35, SW2.P$2
SW3: R46.1, RP3.35, SW3.P$2
SW4: R52.1, RP4.35, SW4.P$2
SWCLK: RP.24, U$2.P$1
SWCLK1: RP1.24, U$3.P$1
SWCLK2: RP2.24, U$4.P$1
SWCLK3: RP3.24, U$5.P$1
SWCLK4: RP4.24, U$6.P$1
SWD: RP.25, U$2.P$2
SWD1: RP1.25, U$3.P$2
SWD2: RP2.25, U$4.P$2
SWD3: RP3.25, U$5.P$2
SWD4: RP4.25, U$6.P$2
T0: R54.2, RP4.38, TMP1.2
T1: R53.2, RP4.39, TMP0.2
TEMP: HEATER.2, R40.2, RP2.40
TRX: ESP32.37, U7.10
TWE_BPS: RP.31, U$1.19
TWE_PGM: RP.12, U$1.2
TWE_RESET: R11.2, RP.30, U$1.21
TWE_RTS: RP.13, U$1.7
TWE_RTX: RP.17, TWE.P$2, U$1.8
TWE_SLEEP: R10.1, RP.29, U$1.27
TWE_TRX: RP.18, TWE.P$1, U$1.9
TX0: RP.27, TOP.2
TX1: BOTTOM.2, RP.6
TX2: C20.2, ESP32.38
TX3: C21.2, ESP32.9
TX4: RP1.27, TOP1.2
TX5: BOTTOM1.2, RP1.6
TX6: RP2.27, TOP2.2
TX7: BOTTOM2.2, RP2.6
TX8: RP3.27, TOP3.2
TX9: BOTTOM3.2, RP3.6
TX10: RP4.27, TOP4.2
TX11: BOTTOM4.2, RP4.6
USB_DM: J1.D-, R1.2
USB_DM1: J2.D-, U7.1
USB_DM2: J3.D-, R21.2
USB_DM3: J4.D-, R28.2
USB_DM4: J5.D-, R41.2
USB_DM5: J6.D-, R47.2
USB_DM_1: R1.1, RP.46
USB_DM_2: R21.1, RP1.46
USB_DM_3: R28.1, RP2.46
USB_DM_4: R41.1, RP3.46
USB_DM_5: R47.1, RP4.46
USB_DP: J1.D+, R2.2
USB_DP1: J2.D+, U7.12
USB_DP2: J3.D+, R22.2
USB_DP3: J4.D+, R29.2
USB_DP4: J5.D+, R42.2
USB_DP5: J6.D+, R48.2
USB_DP_1: R2.1, RP.47
USB_DP_2: R22.1, RP1.47
USB_DP_3: R29.1, RP2.47
USB_DP_4: R42.1, RP3.47
USB_DP_5: R48.1, RP4.47
USB_VCC: D2.A, J2.VBUS, U7.4
V: C69.+, D7.C, Q2.P2, R35.1, R36.2, R38.2, U11.5
V+: BOTTOM.3, C1.1, D1.C, TOP.3, U2.1, U2.3
V+1: C18.1, C20.3, C21.3, D2.C, U4.1, U4.3
V+2: BOTTOM1.3, C41.1, D3.C, TOP1.3, U8.1, U8.3
V+3: BOTTOM2.3, C57.1, HEATER.1, R35.2, TOP2.3, U9.1, U9.3, U11.4
V+4: BOTTOM3.3, C72.1, D8.C, TOP3.3, U12.1, U12.3
V+5: BOTTOM4.3, C90.1, D9.C, TOP4.3, U14.1, U14.3
VBAT: Q2.P3, U10.3
VDD: C2.1, C3.1, C7.1, C8.1, C9.1, C10.1, C11.1, C14.1, C15.1, C16.2, C17.1, FLASH.8, R7.2, R8.2, R9.2, R10.2, R14.2, RP.1, RP.10, RP.22, RP.26, RP.33, RP.42, RP.43, RP.44, RP.48, RP.49, U1.P2, U1.P14, U2.5, U$1.5
VDD1: C19.1, C22.1, C23.1, C26.1, C30.1, C36.1, C38.1, ESP32.2, MICRO_SD.4, R17.2, U3.1, U3.6, U4.5, U5.1, U5.6, U6.1
VDD2: C39.1, C40.1, C42.1, C43.1, C44.1, C45.1, C46.1, C47.1, C53.1, D4.A, FLASH1.8, GNSS.16, RP1.1, RP1.10, RP1.22, RP1.26, RP1.33, RP1.42, RP1.43, RP1.44, RP1.48, RP1.49, U8.5
VDD3: C55.1, C56.1, C58.1, C59.1, C60.1, C61.1, C62.1, C63.1, FLASH2.8, RP2.1, RP2.10, RP2.22, RP2.26, RP2.33, RP2.42, RP2.43, RP2.44, RP2.48, RP2.49, U9.5
VDD4: C70.1, C71.1, C73.1, C74.1, C75.1, C76.1, C77.1, C78.1, C84.1, C85.1, C87.1, FLASH3.8, FLASH_LOG.8, MICRO_SD1.4, RP3.1, RP3.10, RP3.22, RP3.26, RP3.33, RP3.42, RP3.43, RP3.44, RP3.48, RP3.49, U12.5, U13.2
VDD5: C88.1, C89.1, C91.1, C92.1, C93.1, C94.1, C95.1, C96.1, C102.1, C103.1, C104.1, C105.1, C106.1, FLASH4.8, I2C.1, IC1.3, IC1.28, IC2.2, IC2.6, IC2.8, R55.2, R56.2, R57.2, R58.2, RP4.1, RP4.10, RP4.22, RP4.26, RP4.33, RP4.42, RP4.43, RP4.44, RP4.48, RP4.49, TMP0.1, TMP1.1, U14.5
VPP: D5.C, D6.C, D7.A, Q2.P1, R34.2, U10.4
VSENSE: R38.1, R39.2, RP2.39
VSYNC: CAM.7, ESP32.7
WKUP: R9.1, RP.14, U1.P17
XCLK: CAM.13, ESP32.25
XIN1: C12.1, RP.20, X1.3
XIN2: C51.1, RP1.20, X2.3
XIN3: C67.1, RP2.20, X3.3
XIN4: C82.1, RP3.20, X4.3
XIN5: C100.1, RP4.20, X5.3
XOUT1: R5.2, RP.21
XOUT2: R25.2, RP1.21
XOUT3: R32.2, RP2.21
XOUT4: R45.2, RP3.21
XOUT5: R51.2, RP4.21
